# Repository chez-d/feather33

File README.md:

# feather33
Feather form-factor board with a 1.4GHz quad-core A33 from Allwinner.

For assembly, any <=512MB DDR3L should* work (no MCP). 

A 50p board-to-board connector is added to break out another USB, audio, and parallel RGB among other things

This board is designed to work with OSHPark's 6L service and to be assembled with a stencil and hotplate/hot air.

## Initial Testing
Assembled board works fine and communicates over USB.
2 IMPORTANT THINGS!!!
- You cannot boot from MMC1, sadly I discovered this *after* I got the boards. You'll have to first boot off of a SPI flash then use that to jump onto MMC1.
- DDR is still not confirmed.

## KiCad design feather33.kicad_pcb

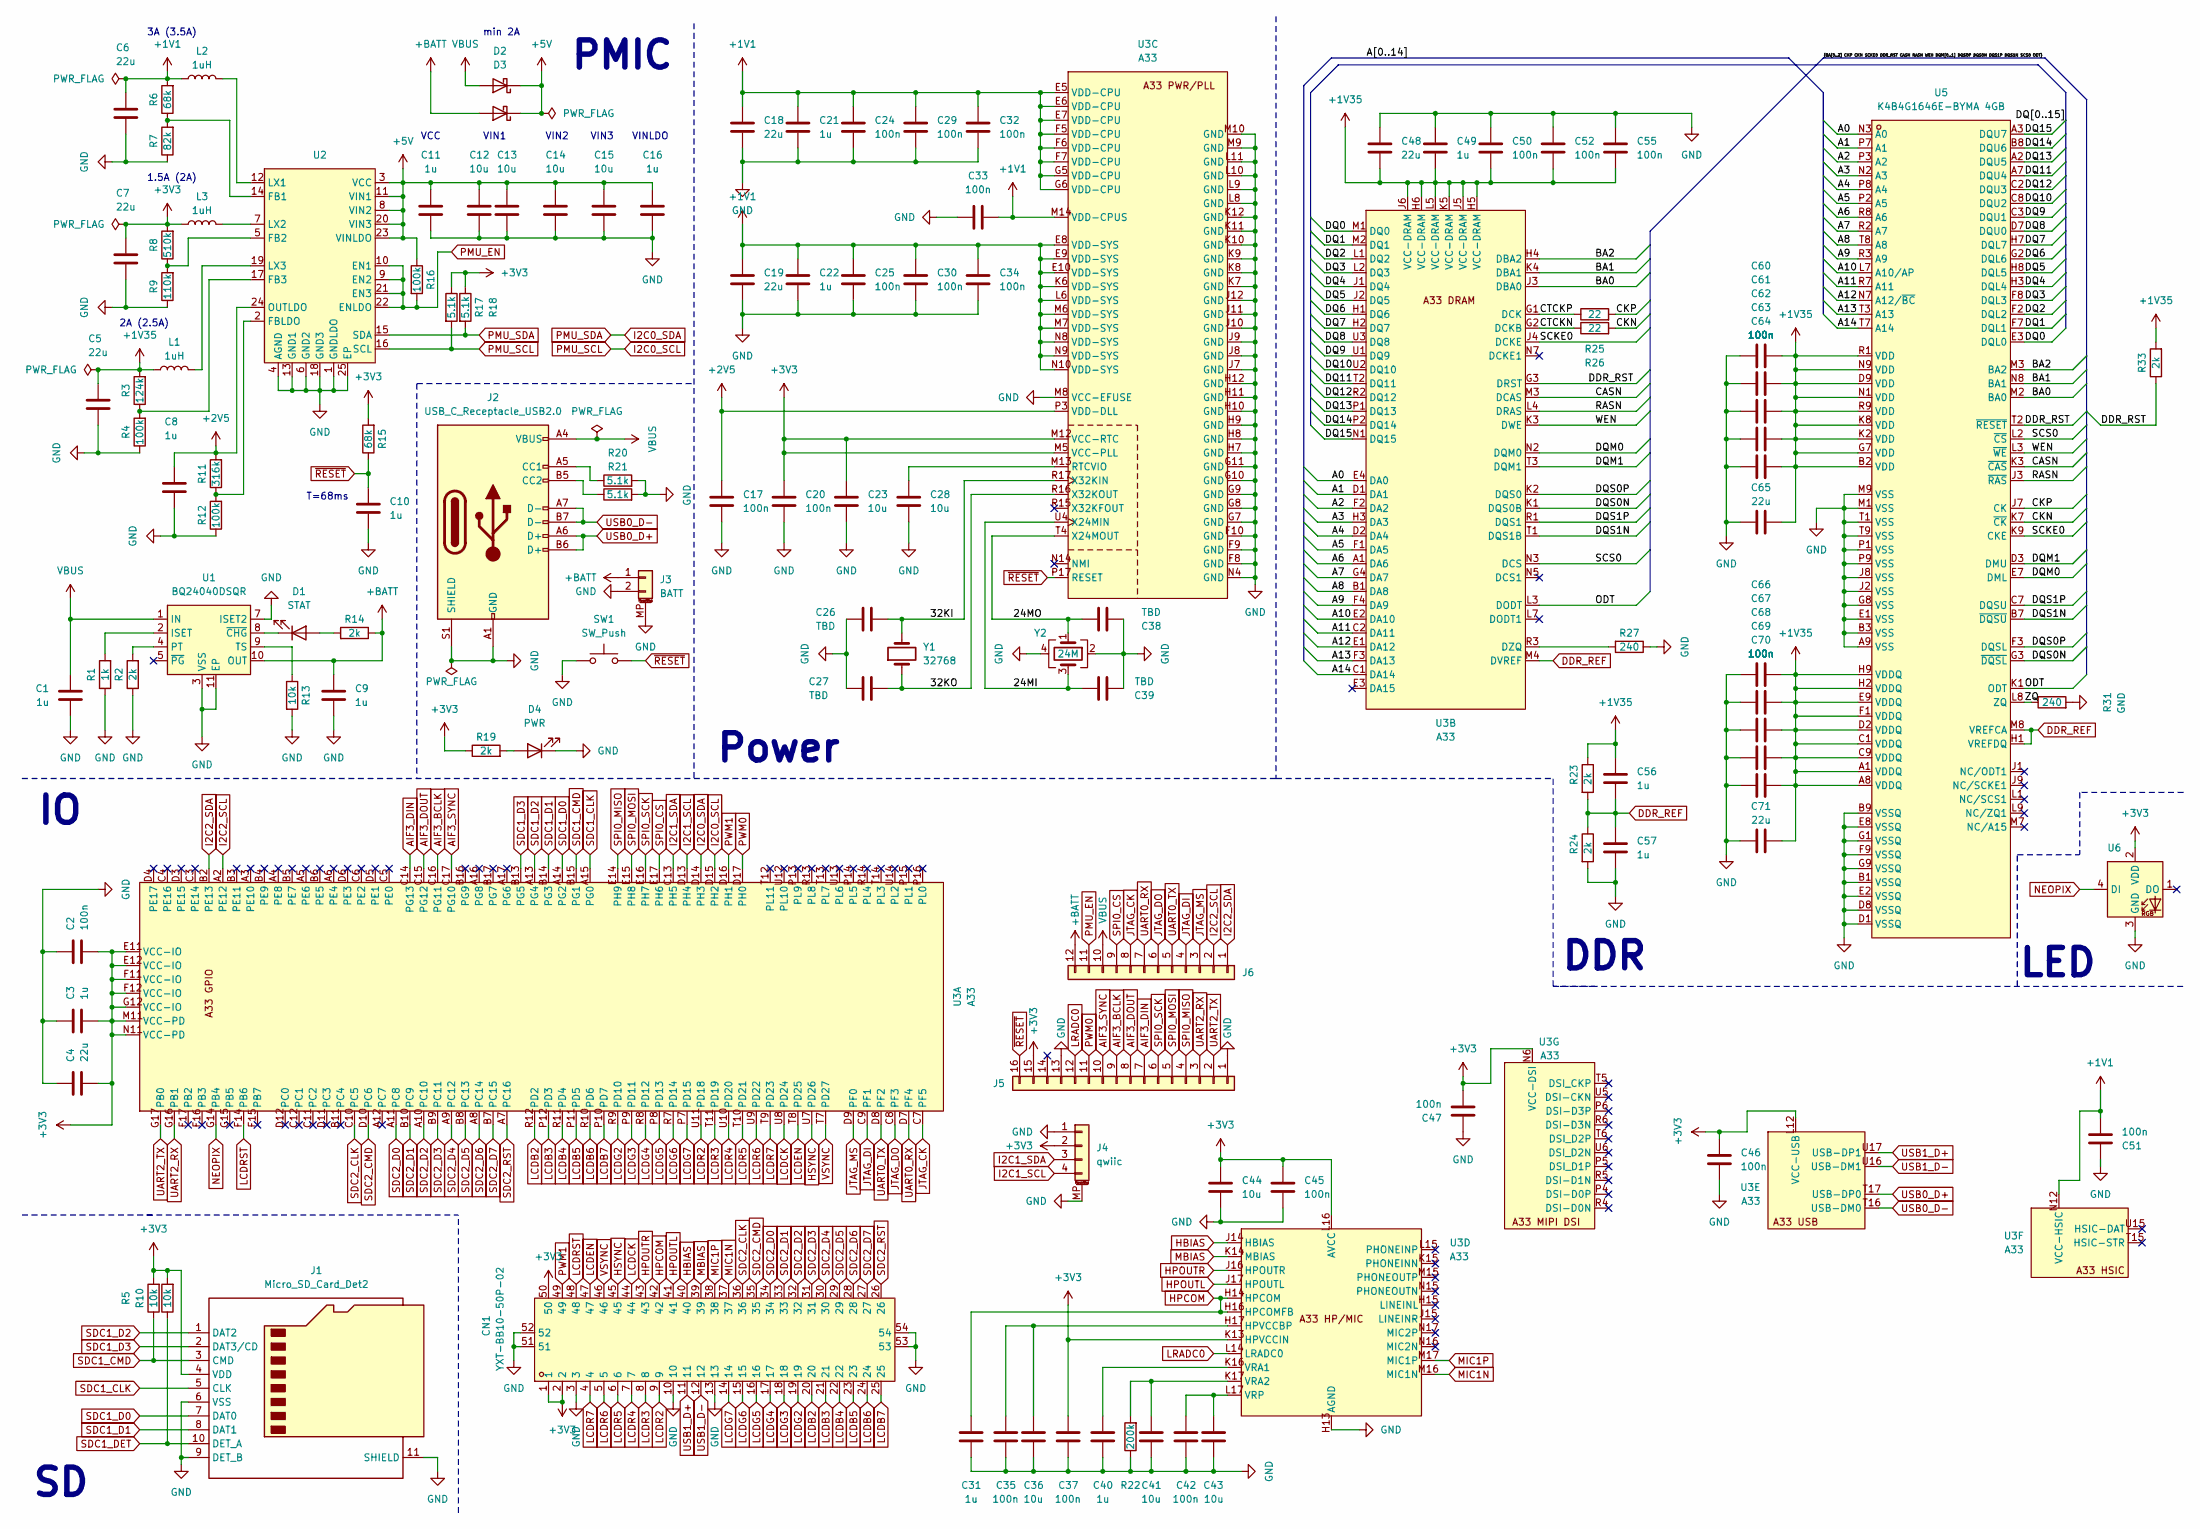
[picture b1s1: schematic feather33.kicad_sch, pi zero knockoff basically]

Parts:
C1, C3, C8, C9, C10, C11, C16, C21, C22, C31, C40, C49, C56, C57: 1u; C_0402_1005Metric
C2, C17, C20, C24, C25, C29, C30, C32, C33, C34, C35, C37, C42, C45, C46, C47, C50, C51, C52, C55, C60, C61, C62, C63, C64, C66, C67, C68, C69, C70: 100n; C_0402_1005Metric
C4, C5, C6, C7, C18, C19, C48, C65, C71: 22u; C_0805_2012Metric
C12, C13, C14, C15, C23, C28, C36, C41, C43, C44: 10u; C_0603_1608Metric
C26, C27, C38, C39: TBD; C_0402_1005Metric
CN1: YXT-BB10-50P-02; CONN-SMD_YXT-BB10-50P-02; LCSC Part C2763977
D1: STAT; LED_0603_1608Metric
D2, D3: D_Schottky; D_SOD-323
D4: PWR; LED_0603_1608Metric
J1: Micro_SD_Card_Det2; microSD_HC_Molex_104031-0811
J2: USB_C_Receptacle_USB2.0; USB-C_SMD-TYPE-C-31-M-12
J3: BATT; CONN-SMD_X2016WRS-02-9TSW
J4: qwiic; JST_SH_BM04B-SRSS-TB_1x04-1MP_P1.00mm_Vertical
J5: Conn_01x16; PinHeader_1x16_P2.54mm_Feather
J6: Conn_01x12; PinHeader_1x12_P2.54mm_Feather
L1, L2, L3: 1uH; IND-SMD_L2.5-W2.0-VLS252012CX-150M
R1: 1k; R_0402_1005Metric
R2, R14, R19, R23, R24, R33: 2k; R_0402_1005Metric
R3: 124k; R_0402_1005Metric
R4, R12, R16: 100k; R_0402_1005Metric
R5, R10, R13: 10k; R_0402_1005Metric
R6, R15: 68k; R_0402_1005Metric
R7: 82k; R_0402_1005Metric
R8: 510k; R_0402_1005Metric
R9: 110k; R_0402_1005Metric
R11: 316k; R_0402_1005Metric
R17, R18, R20, R21: 5.1k; R_0402_1005Metric
R22: 200k; R_0402_1005Metric
R25, R26: 22; R_0402_1005Metric
R27, R31: 240; R_0402_1005Metric
SW1: SW_Push; SW_SPST_PTS810
U1: BQ24040DSQR; WSON-10_L2.0-W2.0-P0.40-BL-EP; LCSC Part C81080
U2: VQFN-24-1EP_4x4mm_P0.5mm_EP2.5x2.5mm
U3: A33; BGA-282_L14.0-W14.0-R17-W17-P0.8-TL
U5: K4B4G1646E-BYMA 4GB; FBGA-96_L13.5-W7.5-R16-C6-P0.80-TL; LCSC Part C500275
U6: NEOPIXEL; LED-SMD_4P-L1.6-W1.5_XL-1615RGBC-WS2812B; LCSC Part C5349954
Y1: 32768; Crystal_SMD_3215-2Pin_3.2x1.5mm
Y2: 24M; Crystal_SMD_2016-4Pin_2.0x1.6mm

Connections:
+1V1: C6.1, C18.1, C19.1, C21.1, C22.1, C24.1, C25.1, C29.1, C30.1, C32.1, C33.2, C34.1, C51.2, L2.1, R6.2, U3.E5 (VDD-CPU), U3.E6 (VDD-CPU), U3.E7 (VDD-CPU), U3.E8 (VDD-SYS), U3.E9 (VDD-SYS), U3.E10 (VDD-SYS), U3.F5 (VDD-CPU), U3.F6 (VDD-CPU), U3.F7 (VDD-CPU), U3.G5 (VDD-CPU), U3.G6 (VDD-CPU), U3.K6 (VDD-SYS), U3.L6 (VDD-SYS), U3.M6 (VDD-SYS), U3.M7 (VDD-SYS), U3.M14 (VDD-CPUS), U3.N8 (VDD-SYS), U3.N9 (VDD-SYS), U3.N10 (VDD-SYS), U3.N12 (VCC-HSIC)
+1V35: C5.1, C48.2, C49.2, C50.2, C52.2, C55.2, C56.1, C60.2, C61.2, C62.2, C63.2, C64.2, C65.2, C66.2, C67.2, C68.2, C69.2, C70.2, C71.2, L1.1, R3.2, R23.1, R33.2, U3.H5 (VCC-DRAM), U3.H6 (VCC-DRAM), U3.J5 (VCC-DRAM), U3.J6 (VCC-DRAM), U3.K5 (VCC-DRAM), U3.L5 (VCC-DRAM), U5.A1 (VDDQ), U5.A8 (VDDQ), U5.B2 (VDD), U5.C1 (VDDQ), U5.C9 (VDDQ), U5.D2 (VDDQ), U5.D9 (VDD), U5.E9 (VDDQ), U5.F1 (VDDQ), U5.G7 (VDD), U5.H2 (VDDQ), U5.H9 (VDDQ), U5.K2 (VDD), U5.K8 (VDD), U5.N1 (VDD), U5.N9 (VDD), U5.R1 (VDD), U5.R9 (VDD)
+2V5: C8.1, C17.1, R11.2, U2.24 (OUTLDO), U3.P3 (VDD-DLL)
+3V3: C2.2, C3.2, C4.2, C7.1, C20.1, C23.1, C37.1, C44.1, C45.1, C46.1, C47.2, CN1.1, CN1.2, CN1.50, J1.4 (VDD), J4.2, J5.15, L3.1, R5.2, R8.2, R10.2, R15.2, R17.1, R18.1, R19.1, U3.E11 (VCC-IO), U3.E12 (VCC-IO), U3.F11 (VCC-IO), U3.F12 (VCC-IO), U3.G12 (VCC-IO), U3.K13 (HPVCCIN), U3.L12 (VCC-USB), U3.L16 (AVCC), U3.M5 (VCC-PLL), U3.M11 (VCC-PD), U3.M12 (VCC-RTC), U3.N6 (VCC-DSI), U3.N11 (VCC-PD), U6.2 (VDD)
+5V: C11.1, C12.1, C13.1, C14.1, C15.1, C16.1, D2.1 (K), D3.1 (K), R16.1, U2.3 (VCC), U2.8 (VIN2), U2.11 (VIN1), U2.20 (VIN3), U2.23 (VINLDO)
+BATT: C9.1, D3.2 (A), J3.1, J6.12, R14.1, U1.10 (OUT)
/24MI: C39.2, U3.U4 (X24MIN), Y2.3
/24MO: C38.2, U3.T4 (X24MOUT), Y2.1
/32KI: C26.2, U3.R17 (X32KIN), Y1.2
/32KO: C27.2, U3.R16 (X32KOUT), Y1.1
/A0: U3.E4 (DA0), U5.N3 (A0)
/A1: U3.D1 (DA1), U5.P7 (A1)
/A2: U3.F2 (DA2), U5.P3 (A2)
/A3: U3.H3 (DA3), U5.N2 (A3)
/A4: U3.D2 (DA4), U5.P8 (A4)
/A5: U3.F1 (DA5), U5.P2 (A5)
/A6: U3.A1 (DA6), U5.R8 (A6)
/A7: U3.G4 (DA7), U5.R2 (A7)
/A8: U3.B1 (DA8), U5.T8 (A8)
/A9: U3.F4 (DA9), U5.R3 (A9)
/A10: U3.E2 (DA10), U5.L7 (A10/AP)
/A11: U3.C2 (DA11), U5.R7 (A11)
/A12: U3.E1 (DA12), U5.N7 (A12/~BC)
/A13: U3.F3 (DA13), U5.T3 (A13)
/A14: U3.C1 (DA14), U5.T7 (A14)
/BA0: U3.J3 (DBA0), U5.M2 (BA0)
/BA1: U3.K4 (DBA1), U5.N8 (BA1)
/BA2: U3.H4 (DBA2), U5.M3 (BA2)
/CASN: U3.M3 (DCAS), U5.K3 (~CAS)
/CKN: R26.2, U5.K7 (~CK)
/CKP: R25.2, U5.J7 (CK)
/CTCKN: R26.1, U3.G2 (DCKB)
/CTCKP: R25.1, U3.G1 (DCK)
/DDR_RST: R33.1, U3.G3 (DRST), U5.T2 (~RESET)
/DQ0: U3.M1 (DQ0), U5.E3 (DQL0)
/DQ1: U3.M2 (DQ1), U5.F7 (DQL1)
/DQ2: U3.L1 (DQ2), U5.F2 (DQL2)
/DQ3: U3.L2 (DQ3), U5.F8 (DQL3)
/DQ4: U3.J1 (DQ4), U5.H3 (DQL4)
/DQ5: U3.J2 (DQ5), U5.H8 (DQL5)
/DQ6: U3.H1 (DQ6), U5.G2 (DQL6)
/DQ7: U3.H2 (DQ7), U5.H7 (DQL7)
/DQ8: U3.U3 (DQ8), U5.D7 (DQU0)
/DQ9: U3.U1 (DQ9), U5.C3 (DQU1)
/DQ10: U3.U2 (DQ10), U5.C8 (DQU2)
/DQ11: U3.T2 (DQ11), U5.A7 (DQU4)
/DQ12: U3.R2 (DQ12), U5.C2 (DQU3)
/DQ13: U3.P1 (DQ13), U5.A2 (DQU5)
/DQ14: U3.P2 (DQ14), U5.B8 (DQU6)
/DQ15: U3.N1 (DQ15), U5.A3 (DQU7)
/DQM0: U3.N2 (DQM0), U5.E7 (DML)
/DQM1: U3.T3 (DQM1), U5.D3 (DMU)
/DQS0N: U3.K1 (DQS0B), U5.G3 (~DQSL)
/DQS0P: U3.K2 (DQS0), U5.F3 (DQSL)
/DQS1N: U3.T1 (DQS1B), U5.B7 (~DQSU)
/DQS1P: U3.R1 (DQS1), U5.C7 (DQSU)
/ODT: U3.L3 (DODT), U5.K1 (ODT)
/RASN: U3.L4 (DRAS), U5.J3 (~RAS)
/SCKE0: U3.J4 (DCKE), U5.K9 (CKE)
/SCS0: U3.N3 (DCS), U5.L2 (~CS)
/WEN: U3.K3 (DWE), U5.L3 (~WE)
/ZQ: R31.1, U5.L8 (ZQ)
AIF3_BCLK: J5.9, U3.C16 (PG11)
AIF3_DIN: J5.7, U3.C14 (PG13)
AIF3_DOUT: J5.8, U3.C15 (PG12)
AIF3_SYNC: J5.10, U3.C17 (PG10)
DDR_REF: C56.2, C57.1, R23.2, R24.1, U3.M4 (DVREF), U5.H1 (VREFDQ), U5.M8 (VREFCA)
GND: C1.2, C2.1, C3.1, C4.1, C5.2, C6.2, C7.2, C8.2, C9.2, C10.2, C11.2, C12.2, C13.2, C14.2, C15.2, C16.2, C17.2, C18.2, C19.2, C20.2, C21.2, C22.2, C23.2, C24.2, C25.2, C26.1, C27.1, C28.2, C29.2, C30.2, C31.2, C32.2, C33.1, C34.2, C35.2, C36.2, C37.2, C38.1, C39.1, C40.2, C41.2, C42.2, C43.2, C44.2, C45.2, C46.2, C47.1, C48.1, C49.1, C50.1, C51.1, C52.1, C55.1, C57.2, C60.1, C61.1, C62.1, C63.1, C64.1, C65.1, C66.1, C67.1, C68.1, C69.1, C70.1, C71.1, CN1.3, CN1.10, CN1.13, CN1.51, CN1.52, CN1.53, CN1.54, D4.1 (K), J1.6 (VSS), J1.9 (DET_B), J1.11 (SHIELD), J2.A1 (GND), J2.A12 (GND), J2.B1 (GND), J2.B12 (GND), J2.S1 (SHIELD), J3.2, J3.MP (MountPin), J4.1, J4.MP (MountPin), J5.1, J5.13, R1.1, R2.1, R4.1, R7.1, R9.1, R12.1, R13.2, R20.2, R21.2, R22.1, R24.2, R27.1, R31.2, SW1.1, U1.3 (VSS), U1.7 (ISET2), U1.11 (EP), U2.1 (GNDLDO), U2.4 (AGND), U2.6 (GND2), U2.13 (GND1), U2.18 (GND3), U2.25 (EP), U3.F8 (GND), U3.F9 (GND), U3.F10 (GND), U3.G7 (GND), U3.G8 (GND), U3.G9 (GND), U3.G10 (GND), U3.G11 (GND), U3.H7 (GND), U3.H8 (GND), U3.H9 (GND), U3.H10 (GND), U3.H11 (GND), U3.H12 (GND), U3.H13 (AGND), U3.J7 (GND), U3.J8 (GND), U3.J9 (GND), U3.J10 (GND), U3.J11 (GND), U3.J12 (GND), U3.K7 (GND), U3.K8 (GND), U3.K9 (GND), U3.K10 (GND), U3.K11 (GND), U3.K12 (GND), U3.L8 (GND), U3.L9 (GND), U3.L10 (GND), U3.L11 (GND), U3.M8 (VCC-EFUSE), U3.M9 (GND), U3.M10 (GND), U3.N4 (GND), U5.A9 (VSS), U5.B1 (VSSQ), U5.B3 (VSS), U5.B9 (VSSQ), U5.D1 (VSSQ), U5.D8 (VSSQ), U5.E1 (VSS), U5.E2 (VSSQ), U5.E8 (VSSQ), U5.F9 (VSSQ), U5.G1 (VSSQ), U5.G8 (VSS), U5.G9 (VSSQ), U5.J2 (VSS), U5.J8 (VSS), U5.M1 (VSS), U5.M9 (VSS), U5.P1 (VSS), U5.P9 (VSS), U5.T1 (VSS), U5.T9 (VSS), U6.3 (GND), Y2.2, Y2.4
HBIAS: CN1.40, U3.J14 (HBIAS)
HPCOM: C31.1, CN1.42, U3.H14 (HPCOM), U3.H16 (HPCOMFB)
HPOUTL: CN1.41, U3.J17 (HPOUTL)
HPOUTR: CN1.43, U3.J16 (HPOUTR)
HSYNC: CN1.45, U3.U7 (PD26)
I2C0_SCL: R17.2, U2.16 (SCL), U3.D15 (PH2)
I2C0_SDA: R18.2, U2.15 (SDA), U3.D14 (PH3)
I2C1_SCL: J4.4, U3.D13 (PH4)
I2C1_SDA: J4.3, U3.C13 (PH5)
I2C2_SCL: J6.2, U3.A2 (PE12)
I2C2_SDA: J6.1, U3.B2 (PE13)
JTAG_CK: J6.8, U3.C7 (PF5)
JTAG_DI: J6.4, U3.C9 (PF1)
JTAG_DO: J6.6, U3.C8 (PF3)
JTAG_MS: J6.3, U3.D9 (PF0)
LCDB2: CN1.20, U3.R12 (PD2)
LCDB3: CN1.21, U3.P12 (PD3)
LCDB4: CN1.22, U3.R11 (PD4)
LCDB5: CN1.23, U3.P11 (PD5)
LCDB6: CN1.24, U3.R10 (PD6)
LCDB7: CN1.25, U3.P10 (PD7)
LCDCK: CN1.44, U3.U8 (PD24)
LCDEN: CN1.47, U3.T8 (PD25)
LCDG2: CN1.19, U3.R9 (PD10)
LCDG3: CN1.18, U3.P9 (PD11)
LCDG4: CN1.17, U3.R8 (PD12)
LCDG5: CN1.16, U3.P8 (PD13)
LCDG6: CN1.15, U3.R7 (PD14)
LCDG7: CN1.14, U3.P7 (PD15)
LCDR2: CN1.9, U3.U11 (PD18)
LCDR3: CN1.8, U3.T11 (PD19)
LCDR4: CN1.7, U3.U10 (PD20)
LCDR5: CN1.6, U3.T10 (PD21)
LCDR6: CN1.5, U3.U9 (PD22)
LCDR7: CN1.4, U3.T9 (PD23)
LCDRST: CN1.48, U3.F14 (PB6)
LRADC0: J5.12, U3.L14 (LRADC0)
MBIAS: CN1.39, U3.K14 (MBIAS)
MIC1N: CN1.37, U3.M16 (MIC1N)
MIC1P: CN1.38, U3.M17 (MIC1P)
NEOPIX: U3.G14 (PB4), U6.4 (DI)
unnamed: D1.2 (A), R14.2
unnamed: D1.1 (K), U1.8 (~CHG)
unnamed: D4.2 (A), R19.2
unnamed: J2.A5 (CC1), R20.1
unnamed: J2.B5 (CC2), R21.1
unnamed: R1.2, U1.2 (ISET)
unnamed: R2.2, U1.4 (PT)
unnamed: R13.1, U1.9 (TS)
unnamed: R6.1, R7.2, U2.14 (FB1)
unnamed: R8.1, R9.2, U2.5 (FB2)
unnamed: R3.1, R4.2, U2.17 (FB3)
unnamed: R11.1, R12.2, U2.2 (FBLDO)
unnamed: L2.2, U2.12 (LX1)
unnamed: L3.2, U2.7 (LX2)
unnamed: L1.2, U2.19 (LX3)
unnamed: R27.2, U3.R3 (DZQ)
unnamed: C28.1, U3.M13 (RTCVIO)
unnamed: C35.1, C36.1, U3.H17 (HPVCCBP)
unnamed: C40.1, U3.K16 (VRA1)
unnamed: C41.1, R22.2, U3.K17 (VRA2)
unnamed: C42.1, C43.1, U3.L17 (VRP)
PMU_EN: J6.11, R16.2, U2.9 (EN2), U2.10 (EN1), U2.21 (EN3), U2.22 (ENLDO)
PWM0: J5.11, U3.D17 (PH0)
PWM1: CN1.49, U3.D16 (PH1)
SDC1_CLK: J1.5 (CLK), U3.A15 (PG0)
SDC1_CMD: J1.3 (CMD), R5.1, U3.B15 (PG1)
SDC1_D0: J1.7 (DAT0), U3.A14 (PG2)
SDC1_D1: J1.8 (DAT1), U3.B14 (PG3)
SDC1_D2: J1.1 (DAT2), U3.A13 (PG4)
SDC1_D3: J1.2 (DAT3/CD), U3.B13 (PG5)
SDC1_DET: J1.10 (DET_A), R10.1
SDC2_CLK: CN1.36, U3.C10 (PC5)
SDC2_CMD: CN1.35, U3.D10 (PC6)
SDC2_D0: CN1.34, U3.A11 (PC8)
SDC2_D1: CN1.33, U3.B10 (PC9)
SDC2_D2: CN1.32, U3.A10 (PC10)
SDC2_D3: CN1.31, U3.B9 (PC11)
SDC2_D4: CN1.30, U3.A9 (PC12)
SDC2_D5: CN1.29, U3.B8 (PC13)
SDC2_D6: CN1.28, U3.A8 (PC14)
SDC2_D7: CN1.27, U3.B7 (PC15)
SDC2_RST: CN1.26, U3.A7 (PC16)
SPI0_CS: J6.9, U3.E17 (PH6)
SPI0_MISO: J5.4, U3.E14 (PH9)
SPI0_MOSI: J5.5, U3.E15 (PH8)
SPI0_SCK: J5.6, U3.E16 (PH7)
UART0_RX: J6.7, U3.D7 (PF4)
UART0_TX: J6.5, U3.D8 (PF2)
UART2_RX: J5.3, U3.G16 (PB1)
UART2_TX: J5.2, U3.G17 (PB0)
USB0_D+: J2.A6 (D+), J2.B6 (D+), U3.T17 (USB-DP0)
USB0_D-: J2.A7 (D-), J2.B7 (D-), U3.T16 (USB-DM0)
USB1_D+: CN1.11, U3.U17 (USB-DP1)
USB1_D-: CN1.12, U3.U16 (USB-DM1)
VBUS: C1.1, D2.2 (A), J2.A4 (VBUS), J2.A9 (VBUS), J2.B4 (VBUS), J2.B9 (VBUS), J6.10, U1.1 (IN)
VSYNC: CN1.46, U3.T7 (PD27)
~RESET: C10.1, J5.16, R15.1, SW1.2, U3.P17 (RESET)

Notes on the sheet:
min 2A
VIN1
T=68ms
PMIC
3A (3.5A)
1.5A (2A)
Power
DDR
2A (2.5A)
VIN2
VIN3
VINLDO
LED
VCC

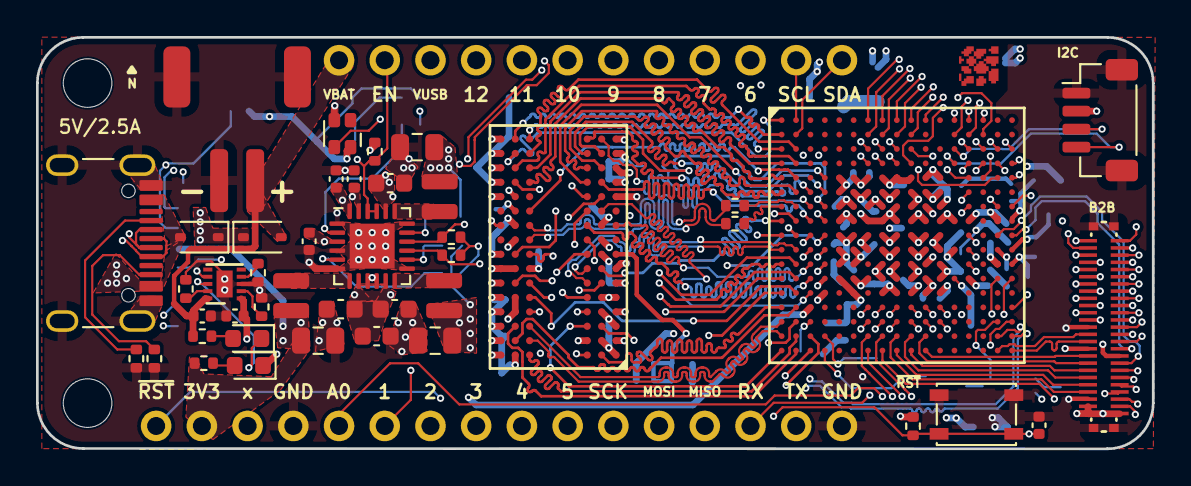
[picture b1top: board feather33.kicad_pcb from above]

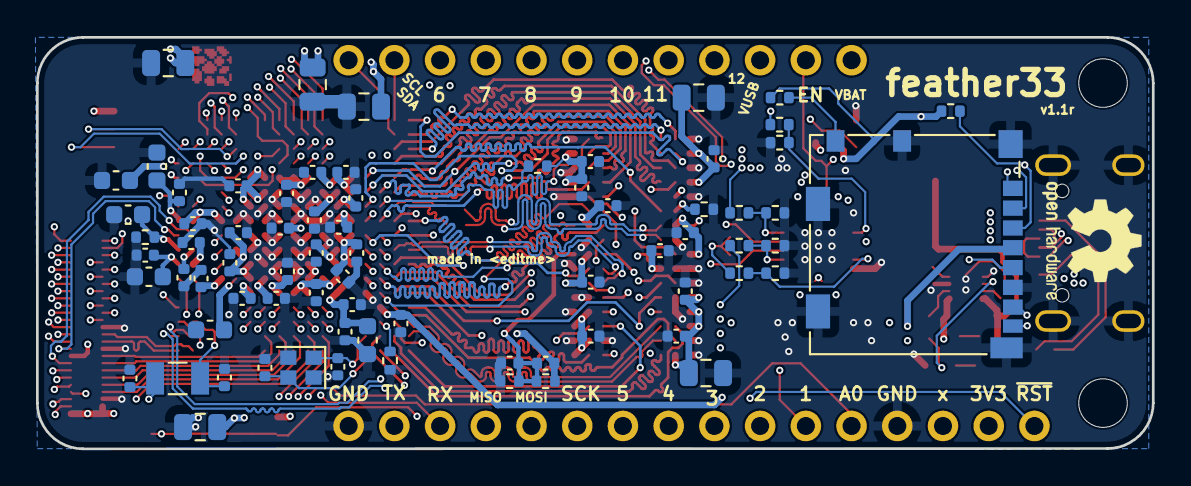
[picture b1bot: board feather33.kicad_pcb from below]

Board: 6 copper layers, 62.0 x 22.9 mm, 118 parts (73 on the bottom side), 166 nets.

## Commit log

2024-04-27 typo
